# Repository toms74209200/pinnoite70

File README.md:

# pinnoite70
70 keys orthogonal keyboard

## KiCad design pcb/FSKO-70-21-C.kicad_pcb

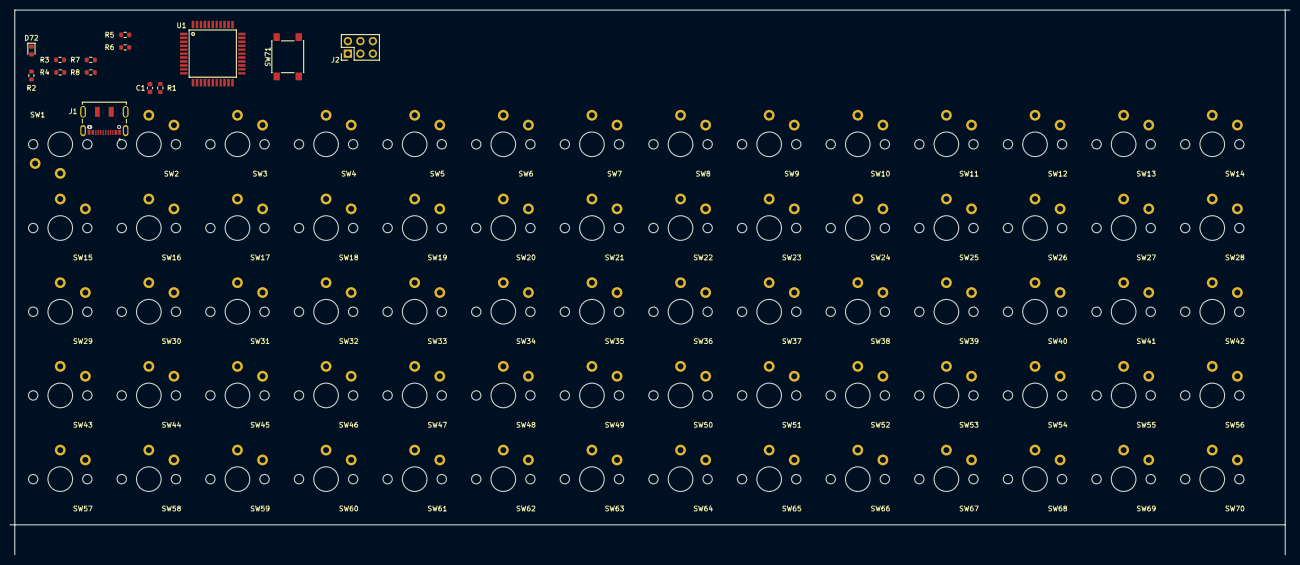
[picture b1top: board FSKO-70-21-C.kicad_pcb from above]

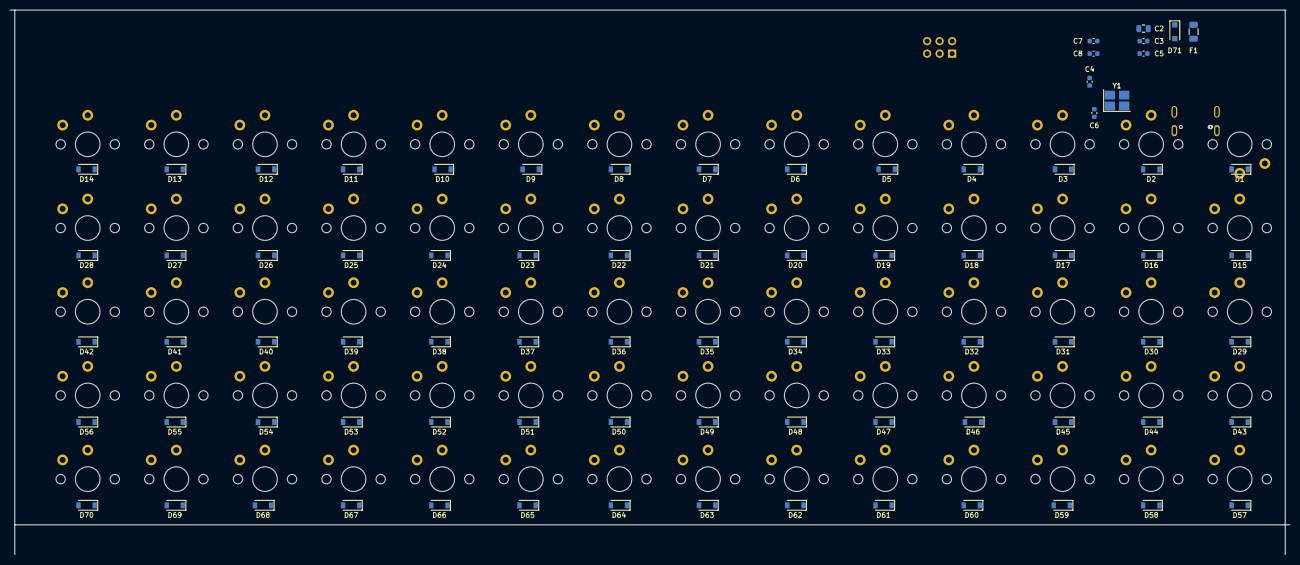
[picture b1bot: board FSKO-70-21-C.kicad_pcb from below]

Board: 2 copper layers, 260.0 x 110.6 mm, 164 parts (80 on the bottom side), 105 nets, no tracks yet.

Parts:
C1, C3, C8: 1u; C_0603_1608Metric
C2: 10u; C_0805_2012Metric
C4, C6: 22p; C_0603_1608Metric
C5, C7: 0.1u; C_0603_1608Metric
D1, D2, D3, D4, D5, D6, D7, D8, D9, D10, D11, D12, D13, D14, D15, D16, D17, D18, D19, D20, D21, D22, D23, D24, D25, D26, D27, D28, D29, D30, D31, D32, D33, D34, D35, D36, D37, D38, D39, D40, D41, D42, D43, D44, D45, D46, D47, D48, D49, D50, D51, D52, D53, D54, D55, D56, D57, D58, D59, D60, D61, D62, D63, D64, D65, D66, D67, D68, D69, D70: 1N4148W; D_SOD-123
D71: RB161MM-20; D_SOD-123F
D72: SMLE13WBC8W1; LED_0603_1608Metric
F1: NANOSMDC050F/13.2; Fuse_1206_3216Metric
J1: DX07S016JA3; JAE_DX07S016JA1R1500
J2: 2x3_F; PinHeader_2x03_P2.54mm_Vertical
R1, R2, R3, R4, R7, R8: 10k; R_0603_1608Metric
R5, R6: 22; R_0603_1608Metric
SW1, SW2, SW3, SW4, SW5, SW6, SW7, SW8, SW9, SW10, SW11, SW12, SW13, SW14, SW15, SW16, SW17, SW18, SW19, SW20, SW21, SW22, SW23, SW24, SW25, SW26, SW27, SW28, SW29, SW30, SW31, SW32, SW33, SW34, SW35, SW36, SW37, SW38, SW39, SW40, SW41, SW42, SW43, SW44, SW45, SW46, SW47, SW48, SW49, SW50, SW51, SW52, SW53, SW54, SW55, SW56, SW57, SW58, SW59, SW60, SW61, SW62, SW63, SW64, SW65, SW66, SW67, SW68, SW69, SW70: SW_Push; Choc_V1_1u
SW71: SW_Push; SW_SPST_PTS645
U1: ATmega32U4-AU; ATMEGA32U4-AU
Y1: 16MHz; Crystal_SMD_SeikoEpson_FA238-4Pin_3.2x2.5mm_HandSoldering

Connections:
+5V: C2.1, C3.1, C5.1, D71.1, J2.2, R1.1, R2.1, U1.14, U1.24, U1.34, U1.44
/A0: SW9.1, SW23.1, SW37.1, SW51.1, SW65.1, U1.36
/A1: SW8.1, SW22.1, SW36.1, SW50.1, SW64.1, U1.37
/A2: SW7.1, SW21.1, SW35.1, SW49.1, SW63.1, U1.38
/A3: SW6.1, SW20.1, SW34.1, SW48.1, SW62.1, U1.39
/COL0: SW1.1, SW15.1, SW29.1, SW43.1, SW57.1, U1.31
/COL1: SW2.1, SW16.1, SW30.1, SW44.1, SW58.1, U1.27
/COL2: SW3.1, SW17.1, SW31.1, SW45.1, SW59.1, U1.1
/COL3: SW4.1, SW18.1, SW32.1, SW46.1, SW60.1, U1.28
/COL4: SW5.1, SW19.1, SW33.1, SW47.1, SW61.1, U1.29
/COL9: J2.3, SW10.1, SW24.1, SW38.1, SW52.1, SW66.1, U1.9
/COL10: J2.1, SW11.1, SW25.1, SW39.1, SW53.1, SW67.1, U1.11
/COL11: J2.4, SW12.1, SW26.1, SW40.1, SW54.1, SW68.1, U1.10
/COL12: SW13.1, SW27.1, SW41.1, SW55.1, SW69.1, U1.30
/COL13: SW14.1, SW28.1, SW42.1, SW56.1, SW70.1, U1.12
/D0: D15.1, D16.1, D17.1, D18.1, D19.1, D20.1, D21.1, D22.1, D23.1, D24.1, D25.1, D26.1, D27.1, D28.1, U1.20
/D1: D1.1, D2.1, D3.1, D4.1, D5.1, D6.1, D7.1, D8.1, D9.1, D10.1, D11.1, D12.1, D13.1, D14.1, U1.21
/D2: D29.1, D30.1, D31.1, D32.1, D33.1, D34.1, D35.1, D36.1, D37.1, D38.1, D39.1, D40.1, D41.1, D42.1, U1.19
/D3: D57.1, D58.1, D59.1, D60.1, D61.1, D62.1, D63.1, D64.1, D65.1, D66.1, D67.1, D68.1, D69.1, D70.1, U1.18
/D4: D43.1, D44.1, D45.1, D46.1, D47.1, D48.1, D49.1, D50.1, D51.1, D52.1, D53.1, D54.1, D55.1, D56.1, U1.25
/D+: R6.1, U1.4
/D-: R5.1, U1.3
/RESET: C1.2, J2.5, R1.2, SW71.1, U1.13
GNDPWR: C1.1, C2.2, C3.2, C4.2, C5.2, C6.2, C7.2, C8.2, D72.1, J1.A1, J1.A12, J2.6, R3.2, R4.2, R7.2, R8.2, SW71.2, U1.5, U1.15, U1.23, U1.33, U1.35, U1.43
unnamed: C4.1, U1.17, Y1.2
unnamed: C6.1, U1.16, Y1.1
unnamed: C7.1, U1.42
unnamed: C8.1, U1.6
unnamed: D1.2, SW1.2
unnamed: D2.2, SW2.2
unnamed: D3.2, SW3.2
unnamed: D4.2, SW4.2
unnamed: D5.2, SW5.2
unnamed: D6.2, SW6.2
unnamed: D7.2, SW7.2
unnamed: D8.2, SW8.2
unnamed: D9.2, SW9.2
unnamed: D10.2, SW10.2
unnamed: D11.2, SW11.2
unnamed: D12.2, SW12.2
unnamed: D13.2, SW13.2
unnamed: D14.2, SW14.2
unnamed: D15.2, SW15.2
unnamed: D16.2, SW16.2
unnamed: D17.2, SW17.2
unnamed: D18.2, SW18.2
unnamed: D19.2, SW19.2
unnamed: D20.2, SW20.2
unnamed: D21.2, SW21.2
unnamed: D22.2, SW22.2
unnamed: D23.2, SW23.2
unnamed: D24.2, SW24.2
unnamed: D25.2, SW25.2
unnamed: D26.2, SW26.2
unnamed: D27.2, SW27.2
unnamed: D28.2, SW28.2
unnamed: D29.2, SW29.2
unnamed: D30.2, SW30.2
unnamed: D31.2, SW31.2
unnamed: D32.2, SW32.2
unnamed: D33.2, SW33.2
unnamed: D34.2, SW34.2
unnamed: D35.2, SW35.2
unnamed: D36.2, SW36.2
unnamed: D37.2, SW37.2
unnamed: D38.2, SW38.2
unnamed: D39.2, SW39.2
unnamed: D40.2, SW40.2
unnamed: D41.2, SW41.2
unnamed: D42.2, SW42.2
unnamed: D43.2, SW43.2
unnamed: D44.2, SW44.2
unnamed: D45.2, SW45.2
unnamed: D46.2, SW46.2
unnamed: D47.2, SW47.2
unnamed: D48.2, SW48.2
unnamed: D49.2, SW49.2
unnamed: D50.2, SW50.2
unnamed: D51.2, SW51.2
unnamed: D52.2, SW52.2
unnamed: D53.2, SW53.2
unnamed: D54.2, SW54.2
unnamed: D55.2, SW55.2
unnamed: D56.2, SW56.2
unnamed: D57.2, SW57.2
unnamed: D58.2, SW58.2
unnamed: D59.2, SW59.2
unnamed: D60.2, SW60.2
unnamed: D61.2, SW61.2
unnamed: D62.2, SW62.2
unnamed: D63.2, SW63.2
unnamed: D64.2, SW64.2
unnamed: D65.2, SW65.2
unnamed: D66.2, SW66.2
unnamed: D67.2, SW67.2
unnamed: D68.2, SW68.2
unnamed: D69.2, SW69.2
unnamed: D70.2, SW70.2
unnamed: D71.2, F1.1
unnamed: D72.2, R2.2
unnamed: J1.A5, R7.1, R8.1
unnamed: J1.A6, J1.B6, R6.2
unnamed: J1.A7, J1.B7, R5.2
unnamed: J1.B5, R3.1, R4.1
VCC: F1.2, J1.A4, J1.A9, U1.2, U1.7

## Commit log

2021-06-20 :sparkles:add layout
2021-06-20 :sparkles:add PCB
2021-06-20 :memo:add layout in README
2021-06-26 :sparkles: add PCB layout
2021-07-03 :sparkles: change key switch
2021-07-22 :fire: delete parts
